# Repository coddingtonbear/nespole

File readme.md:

# Microcontroller-controlled Laminator (Nespole)

Need to control your laminator's temperature precisely because you use it
for performing temperature-specific things like applying photosensitive
dry film to PCBs or trying out the toner transfer method?  This lets you
do that.

## Parts

* [AmazonBasics Thermal Laminator](https://www.amazon.com/AmazonBasics-PL9-US-Thermal-Laminator/dp/B00BUI5QWS); ~$21 as of this writing.
* 120VAC to 5VDC transformer; ~$5
* [MAX6675 and K-Type thermocouple](https://www.amazon.com/HiLetgo-MAX6675-Thermocouple-Temperature-Arduino/dp/B01HT871SO/ref=sr_1_cc_3?s=aps&ie=UTF8&qid=1486343835&sr=1-3-catcorr&keywords=MAX6675);
  ~$5 -- you'll need to remove the chip and mounting pins from the little PCB for attaching to the final board.
* ATMega328pb microcontroller; ~$2 -- an ATMega328p would probably work just as well, but you may need to double-check the pinouts.
* Common-cathode 4-digit 7-segment (+decimal point) Display; ~$1
* AS1108WL common-cathode LED array controller or equivalent; ~$4
* PEC11S Rotary encoder w/ button; ~$3
* CH340G USB-Serial UART adapter; ~$1 -- not strictly necessary if you're comfortable programming the chip via the SPI bus
* CLX6A 3.5mm x 3.5mm RGB LED; &lt;$1
* A relay (for turning the heating element on/off)
* A variety of passives, a diode, a logic-level p-channel mosfet, a logic-level n-channel mosfet (all SOT-23), etc; see the schematic for details.

## Interface

Just turn the rotary encoder to set the target temperature; when you've found
your target temperature, press the rotary in to activate its button.  That's all.

There's a single RGB LED on-board; various LED colors mean various things
including:

* Off: The heating element is off.
* Blue: The unit is starting up.
* White: You are setting the temperature right now.
* Red: The heating element is on.

## Schematics

The included schematics and layout are both correct (as far as I know), but
if you observe the photos linked here, you'll see that they differ in slight
ways.  If you look carefully, you'll see that I've had to correct several
oversights by using bodge wires or, in two cases, installing capacitors that
I neglected to include in the original design.  The attached schematic has,
though, been corrected to account for these oversights.

In case you're curious about the errors I made, they were the following:

* Added the bypass capacitors to the wrong pins of the microcontroller.  I
  did not notice this problem until very late in the game when I was trying
  to diagnose what was causing some erratic behavior.  The root cause of this
  was that I did not pay close-enough attention to which pin was the ADC's
  VCC and which pin was the microcontroller's normal VCC.  Really, though,
  there should be bypass capacitors for both, so I've updated the design
  to include them for both VCCs.
* Neglected to connect the CH340G's GND pin to anything at all.
* Mis-connected the N-Channel mosfet used for switching the laminator's
  relay.  I misread the datasheet and had swapped the source and drain
  pins.
* A couple traces were just a little too close together and had to be cut
  apart during various fabrication steps.

## Earlier Versions

### Nespole 1.0

The first version of nespole was intended to be just a bit simpler; it would
fetch measurements from a thermocouple in a way very similar to what Nespole 2.0
does (except via a slightly-newer MAX31855).  I encountered a ton of trouble
getting the thermocouple chip to return reasonable data, and eventually gave
up and reprogrammed this board to just provide a USB interface for flipping
the relay on-and-off.

## Future Thoughts

There are a couple things I'd perhaps change in a later iteration:

* Spend more time tweaking the layout so I can get the relay control header
  near the top of the board instead of the bottom.  This is something that
  could probably be done without a huge amount of further effort, but
  sometimes it's important to settle for "good enough".
* Place the alignment points off of the final board area instead of within
  it.  When making this board, I was using copper clad that was only very
  slightly larger than the final size and decided to be a little conservative.
* In the end, I used 5566 bytes of flash and only 300 bytes of memory; I could
  probably get by with a lower-powered microcontroller.  It's a little hard to
  beat the price of the ATMega328pb, though, so that might be more of a
  challenge than it is actually worth.

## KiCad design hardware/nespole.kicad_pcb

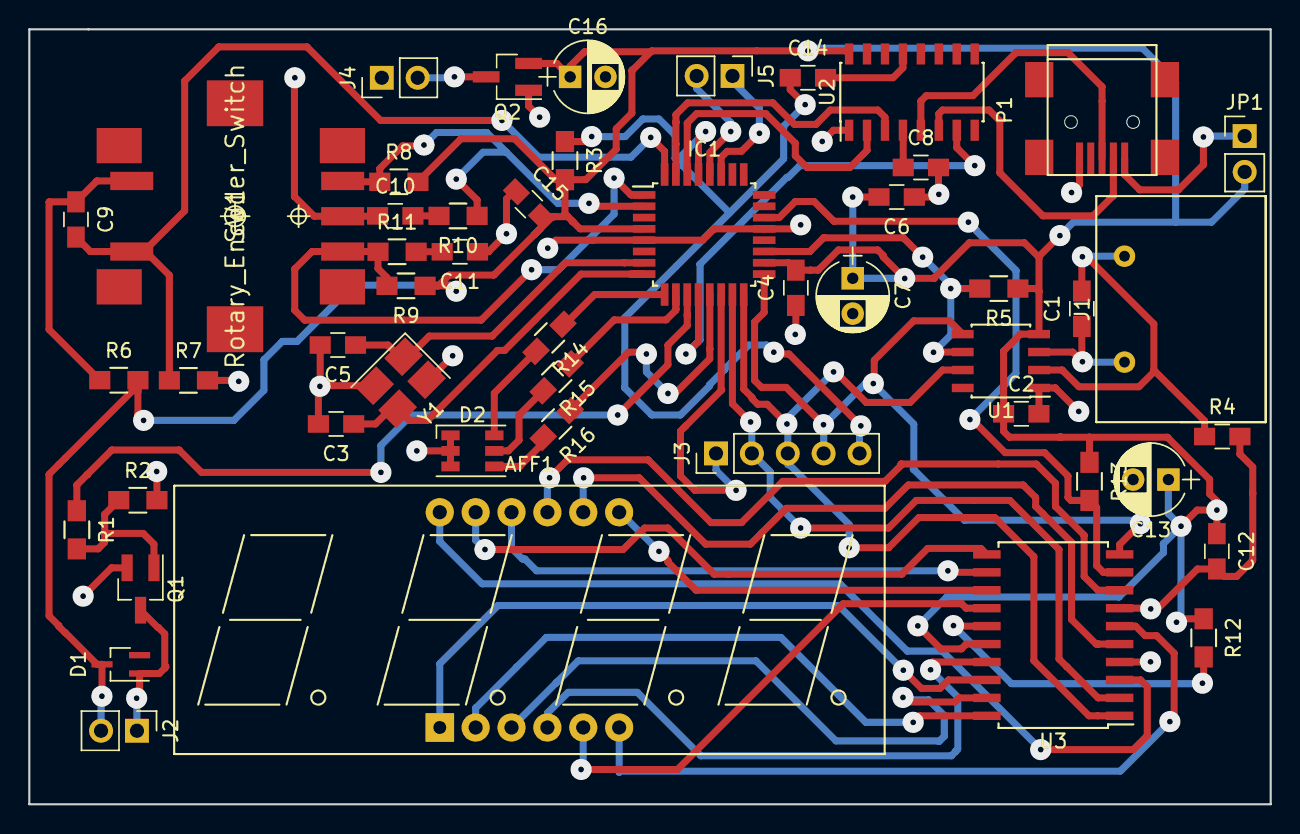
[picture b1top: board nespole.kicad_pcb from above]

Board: 2 copper layers, 87.9 x 54.9 mm, 50 parts (0 on the bottom side), 52 nets.

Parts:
AFF1: CA56-12; Cx56-12
C1, C2, C4, C6, C8, C9, C10, C11, C14, C15: 0.1u; C_0805_HandSoldering
C3, C5: 22p; C_0805_HandSoldering
C7: 10m; CP_Radial_D5.0mm_P2.50mm
C12: 0.1uF; C_0805_HandSoldering
C13: 10u; CP_Radial_D5.0mm_P2.50mm
C16: 22m; CP_Radial_D5.0mm_P2.50mm
D1: D; SOT-323_DIODE
D2: LED_RGB; LED_RGB_PLCC-6
IC1: ATMEGA328PB-A; TQFP-32_7x7mm_Pitch0.8mm
J1: Screw_Terminal_1x02; 01x02_7.5mm_Header_Screw_Terminal
J2, J4, J5: Screw_Terminal_1x02; Pin_Header_Straight_1x02_Pitch2.54mm
J3: Screw_Terminal_1x05; Pin_Header_Straight_1x05_Pitch2.54mm
JP1: Jumper_NO_Small; Pin_Header_Straight_1x02_Pitch2.54mm
P1: USB_OTG; USB_Mini-B
Q1: MOSFET_N_CH; SOT-23_Handsoldering
Q2: MOSFET_P_CH; SOT-23_Handsoldering
R1: 270; R_0805_HandSoldering
R2, R3, R5, R7, R8, R9, R13: 10k; R_0805_HandSoldering
R4: 0; C_0805_HandSoldering
R6, R14, R15: 1k; R_0805_HandSoldering
R10, R11: 2.2k; R_0805_HandSoldering
R12: 9.53k; R_0805_HandSoldering
R16: 1.5k; R_0805_HandSoldering
SW1: Rotary_Encoder_Switch; ROTARY-ENCODER-PEC11S
U1: MAX6675; SOIC-8_3.9x4.9mm_Pitch1.27mm
U2: CH340G; SOIC-16_3.9x9.9mm_Pitch1.27mm
U3: AS1108; SOIC-20W_7.5x12.8mm_Pitch1.27mm
Y1: Crystal_GND24; Crystal_SMD_TXC_7M-4pin_3.2x2.5mm_HandSoldering

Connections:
+5V: C2.1, C4.2, C6.2, C7.1, C12.1, C13.1, C15.2, C16.1, D1.1, IC1.4, IC1.18, J2.2, JP1.2, Q2.S, R3.2, R5.1, R6.2, R8.2, R9.1, R12.1, R13.1, U1.4, U2.16, U3.16
/LED_DIGIT_0: AFF1.12, U3.3
/LED_DIGIT_1: AFF1.9, U3.8
/LED_DIGIT_2: AFF1.8, U3.5
/LED_DIGIT_3: AFF1.6, U3.6
/LED_SEGMENT_A: AFF1.11, U3.11
/LED_SEGMENT_B: AFF1.7, U3.13
/LED_SEGMENT_C: AFF1.4, U3.17
/LED_SEGMENT_D: AFF1.2, U3.20
/LED_SEGMENT_DP: AFF1.3, U3.19
/LED_SEGMENT_E: AFF1.1, U3.18
/LED_SEGMENT_F: AFF1.10, U3.12
/LED_SEGMENT_G: AFF1.5, U3.14
/to_relay: D1.2, J2.1, Q1.D
CLKOUT: IC1.12, U2.7
ENABLE_RELAY: IC1.11, R1.1
GND: C2.2, C3.2, C4.1, C5.2, C6.1, C7.2, C8.2, C10.1, C11.1, C12.2, C13.2, C15.1, C16.2, D2.1, D2.2, D2.3, IC1.5, IC1.21, J4.1, P1.5, Q1.S, Q2.G, R2.2, R4.2, R7.2, SW1.2, U1.1, U2.1, U3.4, U3.7, Y1.2, Y1.4
LED_B: IC1.9, R14.1
LED_CS: IC1.22, R13.2, U3.9
LED_G: IC1.10, R15.1
LED_R: IC1.13, R16.1
MC_CS: IC1.14, J3.1
MISO: IC1.16, J3.3, U1.7, U3.1
MOSI: IC1.15, J3.2, U3.2
unnamed: C1.1, J1.1, U1.3
unnamed: C1.2, J1.2, R4.1, U1.2
unnamed: C3.1, IC1.8, Y1.3
unnamed: C5.1, IC1.7, Y1.1
unnamed: C8.1, U2.4
unnamed: C9.1, R6.1, SW1.5
unnamed: C10.2, R10.2
unnamed: C11.2, R11.2
unnamed: C14.2, U2.13
unnamed: D2.4, R16.2
unnamed: D2.5, R15.2
unnamed: D2.6, R14.2
unnamed: J4.2, Q2.D
unnamed: JP1.1, P1.1
unnamed: P1.2, U2.6
unnamed: P1.3, U2.5
unnamed: Q1.G, R1.2, R2.1
unnamed: R12.2, U3.15
RESET: C14.1, IC1.29, J3.5, R3.1
RXD: IC1.30, U2.2
SCK: IC1.17, J3.4, U1.5, U3.10
SCL: IC1.28, J5.2
SDA: IC1.27, J5.1
SW_BUTTON: C9.2, IC1.32, R7.1, SW1.4
SW_DIR: IC1.2, R8.1, R10.1, SW1.3
SW_INT: IC1.1, R9.2, R11.1, SW1.1
TEMP_CS: IC1.19, R5.2, U1.6
TXD: IC1.31, U2.3

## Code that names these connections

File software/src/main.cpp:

#include "main.h"

#define LED_R 9
#define LED_G 6
#define LED_B 5

#define SW_DIR 4
#define SW_INT 3
#define SW_BUTTON 2

#define CS_TEMP A6
#define CS_LED A7
#define CS_SELF 10

#define EN_RELAY 7

#define TARGET_EEPROM_ADDRESS 100

SPISettings slow(500000, MSBFIRST, SPI_MODE0);


volatile float currentTemperature = 0;
volatile float targetTemperature = 0;
volatile float allowRelay = false;
volatile float thermocoupleAttached = false;
volatile float relayEnabled = false;

volatile unsigned long showTargetUntil = 0;

int freeRam () {
    extern int __heap_start, *__brkval; 
    int v; 
    return (int) &v - (__brkval == 0 ? (int) &__heap_start : (int) __brkval); 
}


ISR(BADISR_vect)
{
    for (;;) UDR0='!';
}

void setup() {
    Serial.begin(9600);
    if(MCUSR) {
        Serial.print("System restarted by reset: ");
        Serial.println(MCUSR, BIN);
        delay(30000);
    }
    MCUSR = 0;

    SPI.begin();
    pinMode(LED_R, OUTPUT);
    pinMode(LED_G, OUTPUT);
    pinMode(LED_B, OUTPUT);

    pinMode(SW_DIR, INPUT);
    pinMode(SW_INT, INPUT);
    pinMode(SW_BUTTON, INPUT);

    pinMode(CS_SELF, INPUT_PULLUP);
    pinMode(CS_TEMP, OUTPUT);
    pinMode(CS_LED, OUTPUT);
    pinMode(EN_RELAY, OUTPUT);

    digitalWrite(EN_RELAY, LOW);
    setLedColor(0, 0, 10);

    targetTemperature = EEPROM.read(TARGET_EEPROM_ADDRESS);
    if(targetTemperature > 200) { // The default is 255 if not prev stored.
        targetTemperature = 0;
    }

    attachInterrupt(digitalPinToInterrupt(SW_BUTTON), onButtonPressed, RISING);
    attachInterrupt(digitalPinToInterrupt(SW_INT), onEncoderTurned, RISING);

    setDisplayRegister(0x0c, 0 | (1 << 7) | (1 << 0)); // -Shutdown
    setDisplayRegister(0x09, 15); // Enable decoding for numbers
    setDisplayRegister(0x0a, 0); // Intensity
    setDisplayRegister(0x0e, 0 | (1 << 3)); // Features
    setDisplayRegister(0x0b, 3); // Display all four digits
}


void onButtonPressed() {
    cli();
    if(!allowRelay) {
        allowRelay = true;
    } else {
        allowRelay = false;
    }
    sei();
}


void onEncoderTurned() {
    cli();
    if(digitalRead(SW_DIR) == LOW) {
        targetTemperature++;
    } else {
        targetTemperature--;
    }
    if (targetTemperature < 0) {
        targetTemperature = 0;
    }
    if (targetTemperature > 200) {
        targetTemperature = 200;
    }
    EEPROM.write(TARGET_EEPROM_ADDRESS, targetTemperature);
    showTargetUntil = millis() + 3000;
    sei();
}


float getTemperature() {
    SPI.beginTransaction(slow);
    digitalWrite(CS_TEMP, LOW);
    delayMicroseconds(10);

    uint16_t tempData;
    tempData = SPI.transfer(0xff) << 8;
    tempData |= SPI.transfer(0xff);

    thermocoupleAttached = true;
    if(tempData & 0x4) {
        thermocoupleAttached = false;
    }

    tempData >>=3;

    delayMicroseconds(10);
    digitalWrite(CS_TEMP, HIGH);
    SPI.endTransaction();

    return tempData * 0.25;
}


void setLedColor(uint8_t r, uint8_t g, uint8_t b) {
    analogWrite(LED_R, r);
    analogWrite(LED_G, g);
    analogWrite(LED_B, b);
}


void setDisplayRegister(byte registerId, byte value) {
    SPI.beginTransaction(slow);
    digitalWrite(CS_LED, LOW);
    delayMicroseconds(10);

    SPI.transfer(registerId);
    SPI.transfer(value);

    delayMicroseconds(10);
    digitalWrite(CS_LED, HIGH);
    SPI.endTransaction();
}


void setDisplayValue(float value) {
    int intValue = (int)(value * 10);

    uint8_t digit0 = (intValue % 10000) / 1000;
    uint8_t digit1 = (intValue % 1000) / 100;
    uint8_t digit2 = (intValue % 100) / 10;
    uint8_t digit3 = (intValue % 10);

    if(digit0) {
        setDisplayRegister(1, digit0);
    } else {
        setDisplayRegister(1, 0xf);
    }
    if(digit1 || digit0) {
        setDisplayRegister(2, digit1);
    } else {
        setDisplayRegister(2, 0xf);
    }
    setDisplayRegister(3, digit2 | (1 << 7));
    setDisplayRegister(4, digit3);
}


void enableRelay() {
    setLedColor(10, 0, 0);
    digitalWrite(EN_RELAY, HIGH);
}

void disableRelay() {
    setLedColor(0, 0, 0);
    digitalWrite(EN_RELAY, LOW);
}


void loop() {
    currentTemperature = getTemperature();
    if(millis() < showTargetUntil) {
        disableRelay();
        setLedColor(10, 10, 10);
        setDisplayValue(targetTemperature);
    } else {
        if(
            (currentTemperature < targetTemperature) &&
            allowRelay &&
            thermocoupleAttached
        ) {
            setDisplayValue(currentTemperature);
            enableRelay();
        } else if(!thermocoupleAttached) {
            for(int i = 1; i<=4; i++) {
                setDisplayRegister(i, 10);
            }
            disableRelay();
        } else {
            setDisplayValue(currentTemperature);
            disableRelay();
        }
    }
    delay(250);
}

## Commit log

2017-01-02 And so it begins...
2017-01-03 First revision board renderings.
2017-01-04 Updating board to use mosfet for switching relay on/off.
2017-01-07 Updating hardware for latest version.
2017-01-08 Updating to use ATMEGA2313; I needed just one more pin :-(.
2017-01-08 Fixing a missing GND trace.
2017-01-09 Just drive the relay directly...this MAX31855 is just not working properly.
2017-01-28 Updating hardware for new display.
2017-01-28 Slightly better layout.
2017-01-28 Cutting groundplane to size; adding edge cuts.
2017-01-28 Adding a keepout area below the 12mhz crystal.
2017-01-28 Updating PDFs.
2017-01-28 Minor layout changes; exposing I2C bus via header.
2017-01-28 Explicitly un-mark LED resistors.
2017-01-28 Whoops; neglected to press the PCB update button.
2017-01-28 I'm glad I checked -- the CH341T has a slightly wider size from normal TSSOP-20s.
2017-01-29 Updating netlist to use new CH341-specific footprint.
2017-01-29 Increase traces to 0.5mm; swap CH341T with CH340G; add USB power jumper.
2017-01-29 Better ground plane unity.
2017-02-05 Updating hardware to correct for...mistakes; finishing-up software.
2017-02-06 Fully-working; fixed schematic to wire the mosfet properly.
2017-02-06 Uploading a descriptive readme.
2017-02-06 Minor readme corrections.
2017-02-06 Clarifying why there are more capacitors.
2017-02-07 This is more accurately called 'firmware', really.
2017-02-20 Adding schematic rendering.
2021-10-07 Adding support for setting/seeing temp over serial.
